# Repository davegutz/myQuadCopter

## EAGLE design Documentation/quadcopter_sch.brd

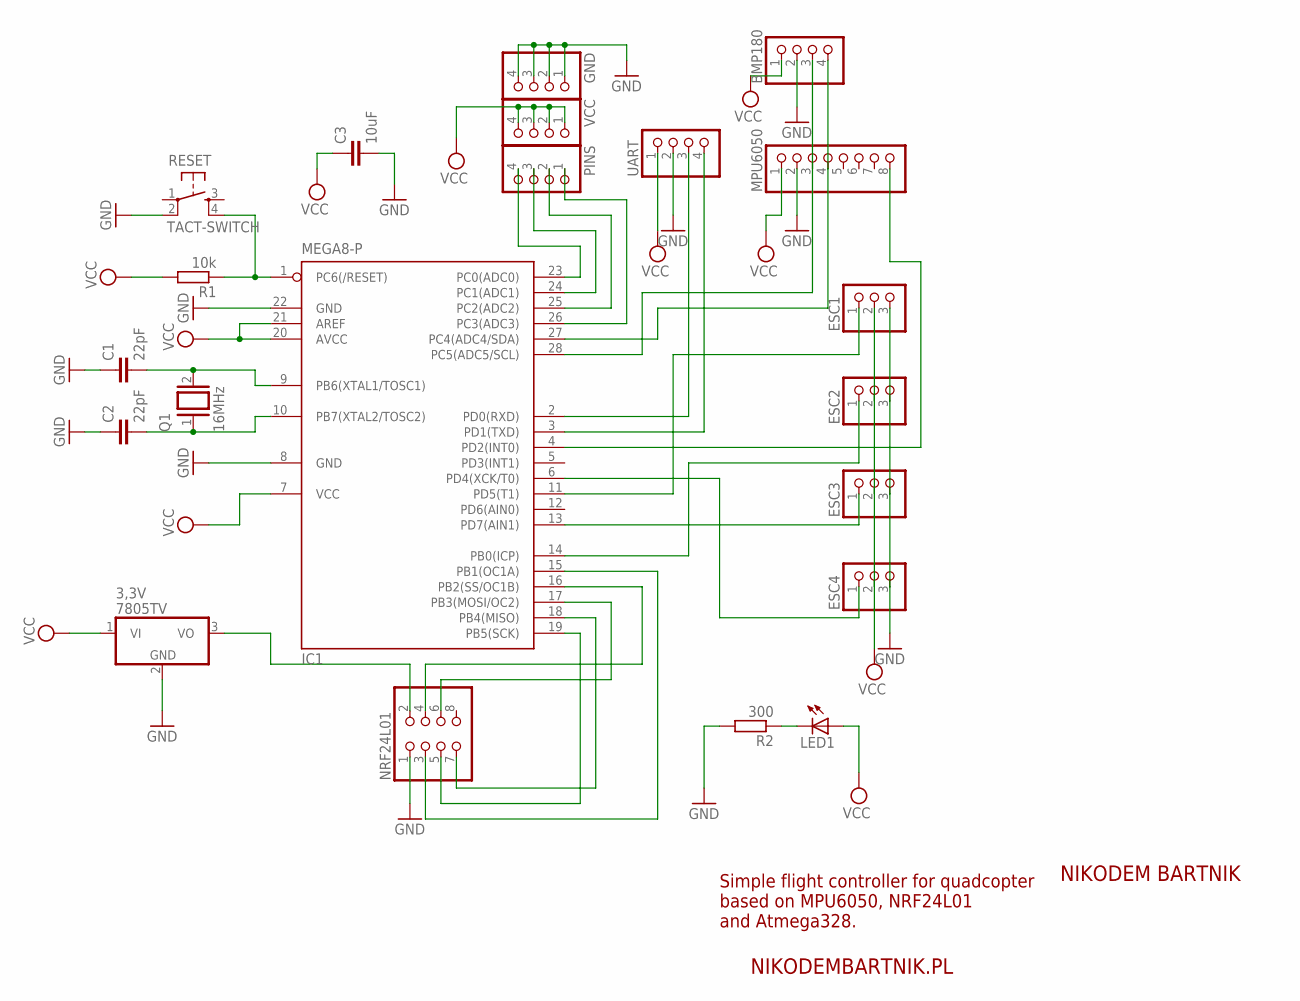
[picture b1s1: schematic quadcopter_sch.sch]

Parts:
3,3V: 7805TV; TO220V
BMP180: PINHD-1X4; 1X04
C1, C2: 22pF; C2.5-3
C3: 10uF; C2.5-3
ESC1, ESC2, ESC3, ESC4: PINHD-1X3; 1X03
GND: PINHD-1X4; 1X04
IC1: MEGA8-P; DIL28-3
LED1: LED5MM
MPU6050: PINHD-1X8; 1X08
NRF24L01: PINHD-2X4; 2X04
PINS: PINHD-1X4; 1X04
Q1: 16MHz; QS
R1: 10k; 0204V
R2: 300; 0204V
RESET: TACT-SWITCH; TAC-SWITCH-PTH
UART: PINHD-1X4; 1X04
VCC: PINHD-1X4; 1X04

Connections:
GND: 3,3V.2 (GND), BMP180.2, C1.1, C2.1, C3.2, ESC1.3, ESC2.3, ESC3.3, ESC4.3, GND.1, GND.2, GND.3, GND.4, IC1.8 (GND), IC1.22 (GND), MPU6050.2, NRF24L01.1, R2.2, RESET.2, UART.2
unnamed: IC1.1 (PC6(/RESET)), R1.1, RESET.4
unnamed: C1.2, IC1.9 (PB6(XTAL1/TOSC1)), Q1.2
unnamed: C2.2, IC1.10 (PB7(XTAL2/TOSC2)), Q1.1
unnamed: IC1.2 (PD0(RXD)), UART.3
unnamed: ESC1.1, IC1.11 (PD5(T1))
unnamed: ESC2.1, IC1.14 (PB0(ICP))
unnamed: ESC3.1, IC1.13 (PD7(AIN1))
unnamed: ESC4.1, IC1.6 (PD4(XCK/T0))
unnamed: IC1.3 (PD1(TXD)), UART.4
unnamed: BMP180.4, IC1.27 (PC4(ADC4/SDA)), MPU6050.4
unnamed: BMP180.3, IC1.28 (PC5(ADC5/SCL)), MPU6050.3
unnamed: IC1.4 (PD2(INT0)), MPU6050.8
unnamed: IC1.23 (PC0(ADC0)), PINS.4
unnamed: IC1.24 (PC1(ADC1)), PINS.3
unnamed: 3,3V.3 (VO), NRF24L01.2
unnamed: IC1.17 (PB3(MOSI/OC2)), NRF24L01.6
unnamed: IC1.18 (PB4(MISO)), NRF24L01.7
unnamed: IC1.19 (PB5(SCK)), NRF24L01.5
unnamed: IC1.15 (PB1(OC1A)), NRF24L01.3
unnamed: IC1.16 (PB2(SS/OC1B)), NRF24L01.4
unnamed: IC1.25 (PC2(ADC2)), PINS.2
unnamed: IC1.26 (PC3(ADC3)), PINS.1
unnamed: LED1.K (C), R2.1
VCC: 3,3V.1 (VI), BMP180.1, C3.1, ESC1.2, ESC2.2, ESC3.2, ESC4.2, IC1.7 (VCC), IC1.20 (AVCC), IC1.21 (AREF), LED1.A, MPU6050.1, R1.2, UART.1, VCC.1, VCC.2, VCC.3, VCC.4

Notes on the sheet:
NIKODEM BARTNIK
NIKODEMBARTNIK.PL
Simple flight controller for quadcopter based on MPU6050, NRF24L01 and Atmega328.

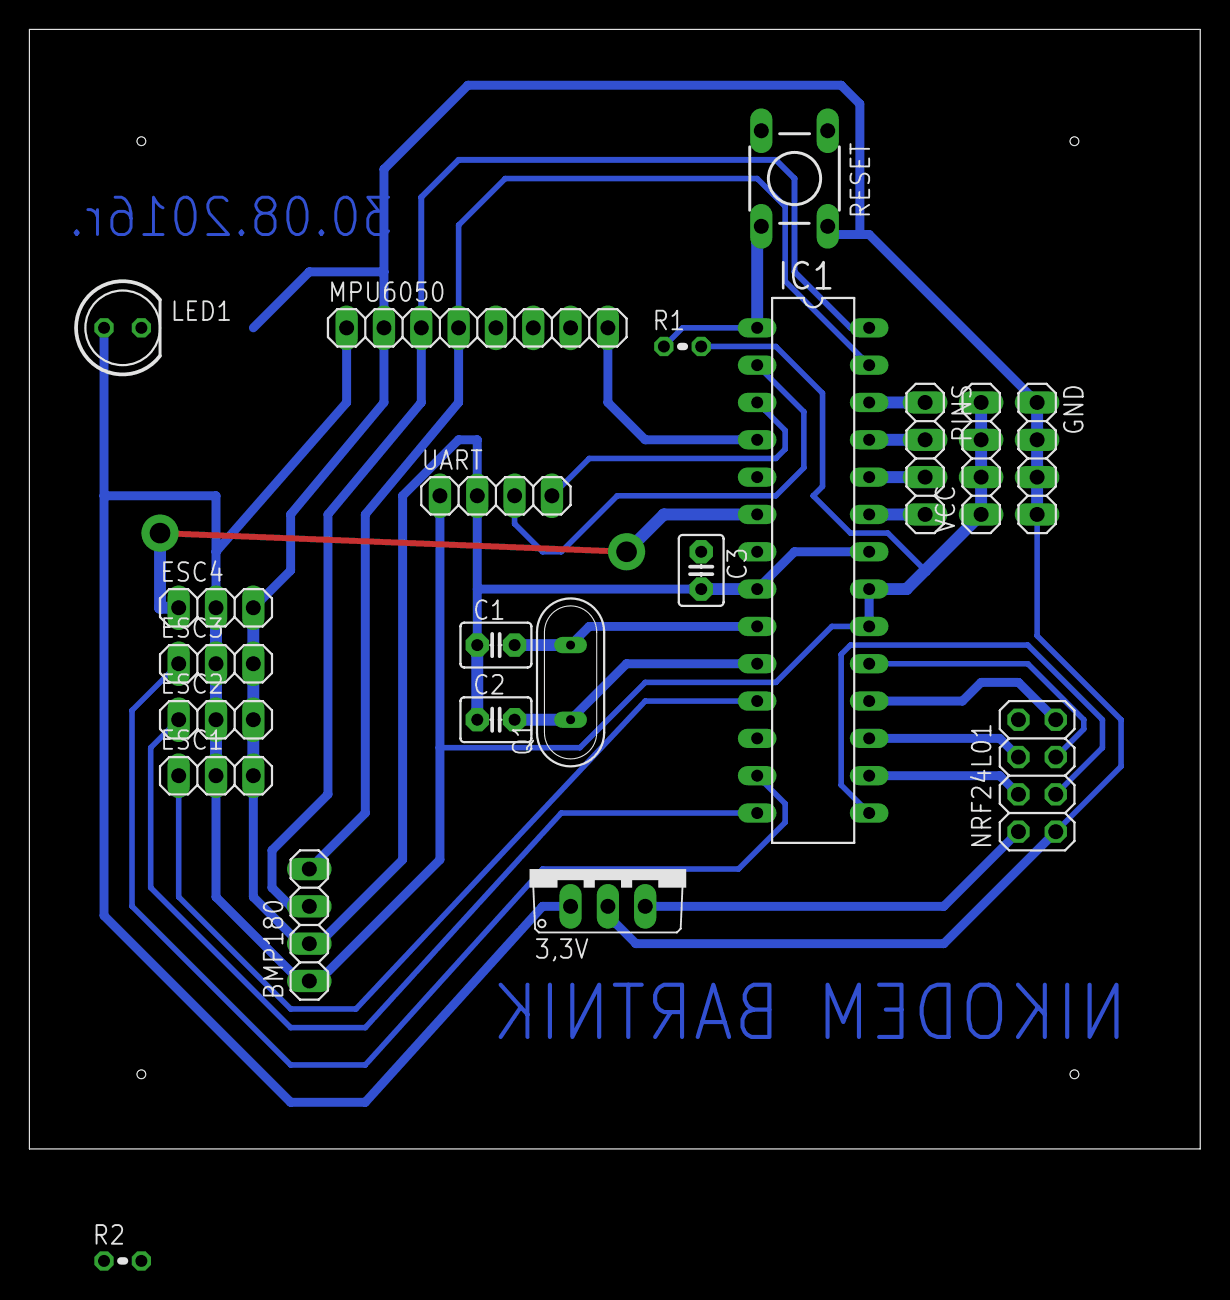
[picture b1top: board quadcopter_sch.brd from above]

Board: 2 copper layers, 79.7 x 76.2 mm, 21 parts (0 on the bottom side), 25 nets.

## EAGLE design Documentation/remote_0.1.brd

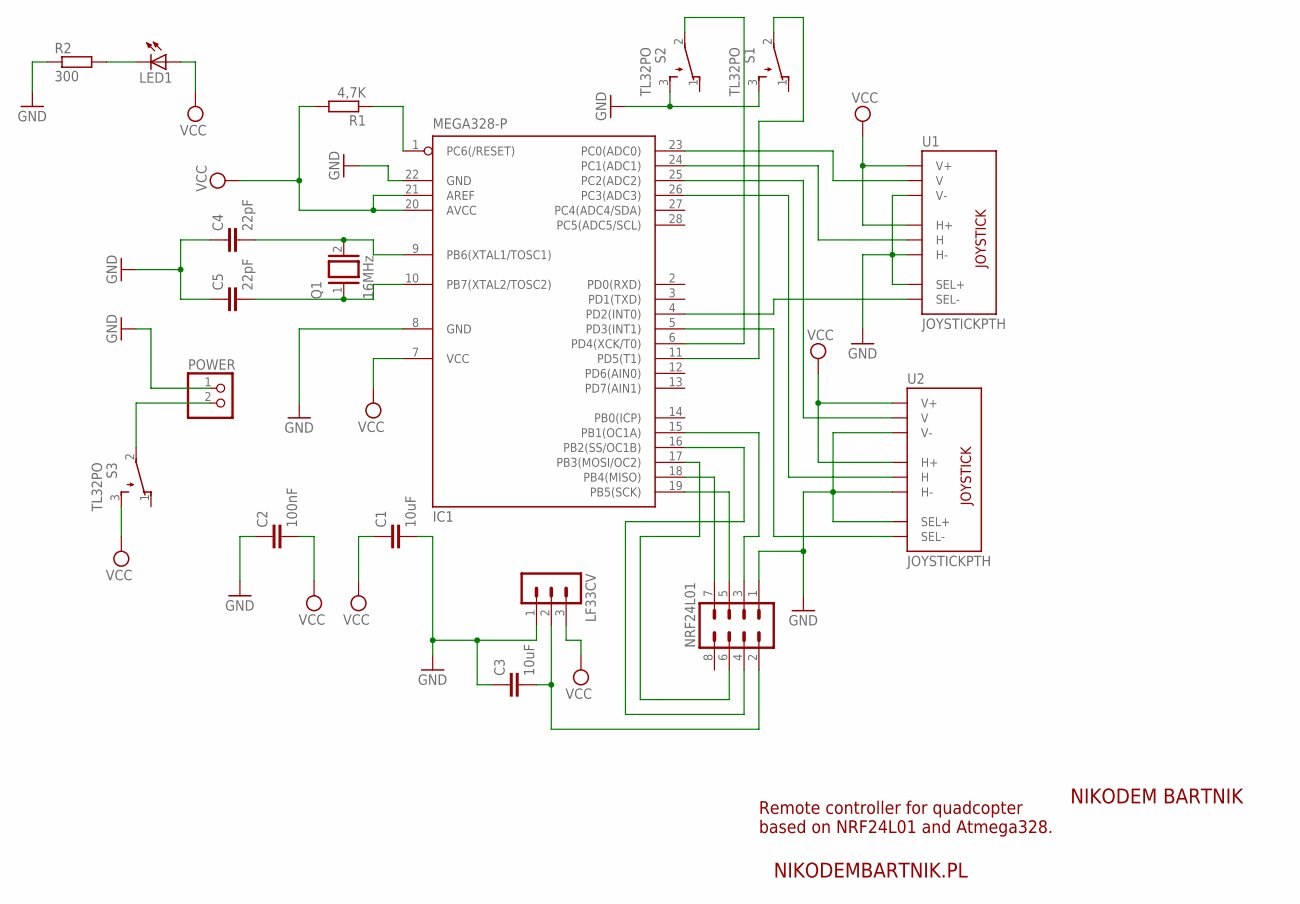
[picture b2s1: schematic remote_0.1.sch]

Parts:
C1, C3: 10uF; C2.5-3
C2: 100nF; C2.5-3
C4, C5: 22pF; CAP-PTH-SMALL-KIT
IC1: MEGA328-P; DIL28-3
LED1: LED5MM
LF33CV: MA03-1
NRF24L01: MA04-2
POWER: PINHD-1X2; 1X02
Q1: 16MHz; QS
R1: 4,7K; 0204/7
R2: 300; 0204/5
S1, S2, S3: TL32PO; TL3XPO
U1, U2: JOYSTICKPTH; JOYSTICK

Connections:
GND: C1.2, C2.1, C3.1, C4.1, C5.1, IC1.8 (GND), IC1.22 (GND), LF33CV.1, NRF24L01.1, POWER.1, R2.1, S1.3 (S), S2.3 (S), U1.B1A (SEL+), U1.H3 (H-), U1.V3 (V-), U2.B1A (SEL+), U2.H3 (H-), U2.V3 (V-)
unnamed: C4.2, IC1.9 (PB6(XTAL1/TOSC1)), Q1.2
unnamed: C5.2, IC1.10 (PB7(XTAL2/TOSC2)), Q1.1
unnamed: IC1.23 (PC0(ADC0)), U1.V2 (V)
unnamed: IC1.24 (PC1(ADC1)), U1.H2 (H)
unnamed: IC1.1 (PC6(/RESET)), R1.1
unnamed: IC1.18 (PB4(MISO)), NRF24L01.7
unnamed: IC1.25 (PC2(ADC2)), U2.V2 (V)
unnamed: IC1.26 (PC3(ADC3)), U2.H2 (H)
unnamed: IC1.4 (PD2(INT0)), U1.B2A (SEL-)
unnamed: IC1.5 (PD3(INT1)), U2.B2A (SEL-)
unnamed: IC1.15 (PB1(OC1A)), NRF24L01.3
unnamed: IC1.16 (PB2(SS/OC1B)), NRF24L01.4
unnamed: IC1.19 (PB5(SCK)), NRF24L01.5
unnamed: IC1.17 (PB3(MOSI/OC2)), NRF24L01.6
unnamed: POWER.2, S3.2
unnamed: C3.2, LF33CV.2, NRF24L01.2
unnamed: IC1.6 (PD4(XCK/T0)), S2.2
unnamed: IC1.11 (PD5(T1)), S1.2
unnamed: LED1.K (C), R2.2
VCC: C1.1, C2.2, IC1.7 (VCC), IC1.20 (AVCC), IC1.21 (AREF), LED1.A, LF33CV.3, R1.2, S3.3 (S), U1.H1 (H+), U1.V1 (V+), U2.H1 (H+), U2.V1 (V+)

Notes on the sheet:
Remote controller for quadcopter based on NRF24L01 and Atmega328.
NIKODEM BARTNIK
NIKODEMBARTNIK.PL

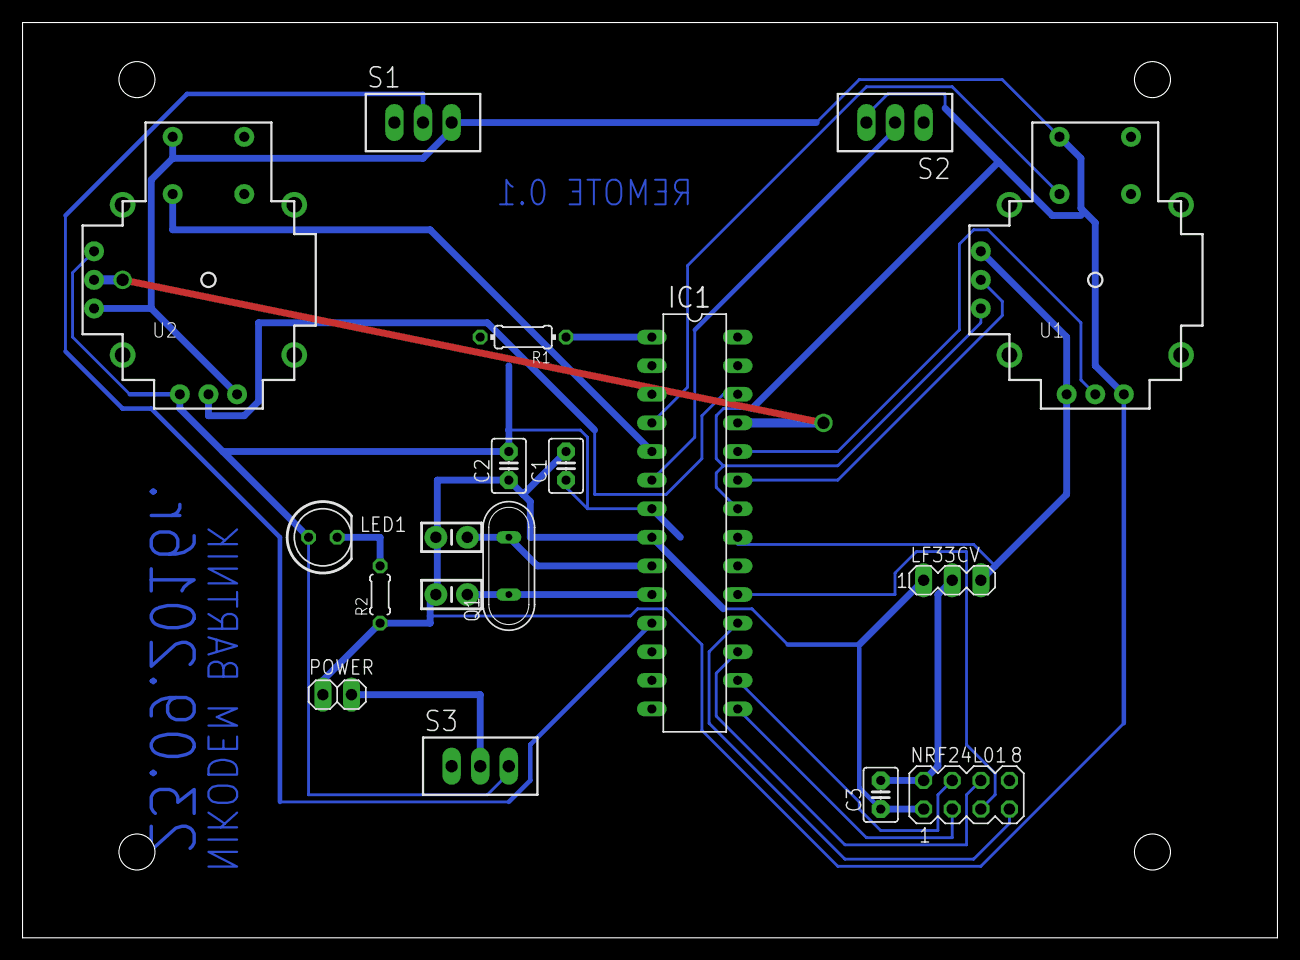
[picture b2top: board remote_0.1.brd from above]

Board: 2 copper layers, 111.4 x 81.3 mm, 18 parts (0 on the bottom side), 21 nets.

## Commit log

2017-04-20 :boom::camel: Added .gitattributes & .gitignore files
2017-04-20 Arduino Quad

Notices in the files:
parts and their libraries:
GeekAmmo: Licensing:Creative Commons ShareAlike 4.0 International - https://creativecommons.org/licenses/by-sa/4.0
